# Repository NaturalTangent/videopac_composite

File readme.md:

# Videopac G7000 Composite Video

This is a PCB providing composite video amplification for a PAL VideoPac G7000.

Created using kicad 6.0.0

## Schematic

The schematic is copied from https://gamesx.com/wiki/doku.php?id=av:g7000_av

## PCB

The PCB measures 60.5mm X 23.5mm.

## BOM

[videopac_rgb_bom.csv](videopac_composite_bom.csv "BOM")

## Installation

Check the schematic for your variant of Videopac PCB, I'm led to believe that different revisions have different IC references and locations.

On the revision I tested with the IC are located as illustrated below (I desoldered the shield to access IC679 to confirm its identity, it's not essntial to do this);

Viewing from the top of the PCB, the location of the input pins are illustrated below;

I soldered to the bottom of the board as shown below;

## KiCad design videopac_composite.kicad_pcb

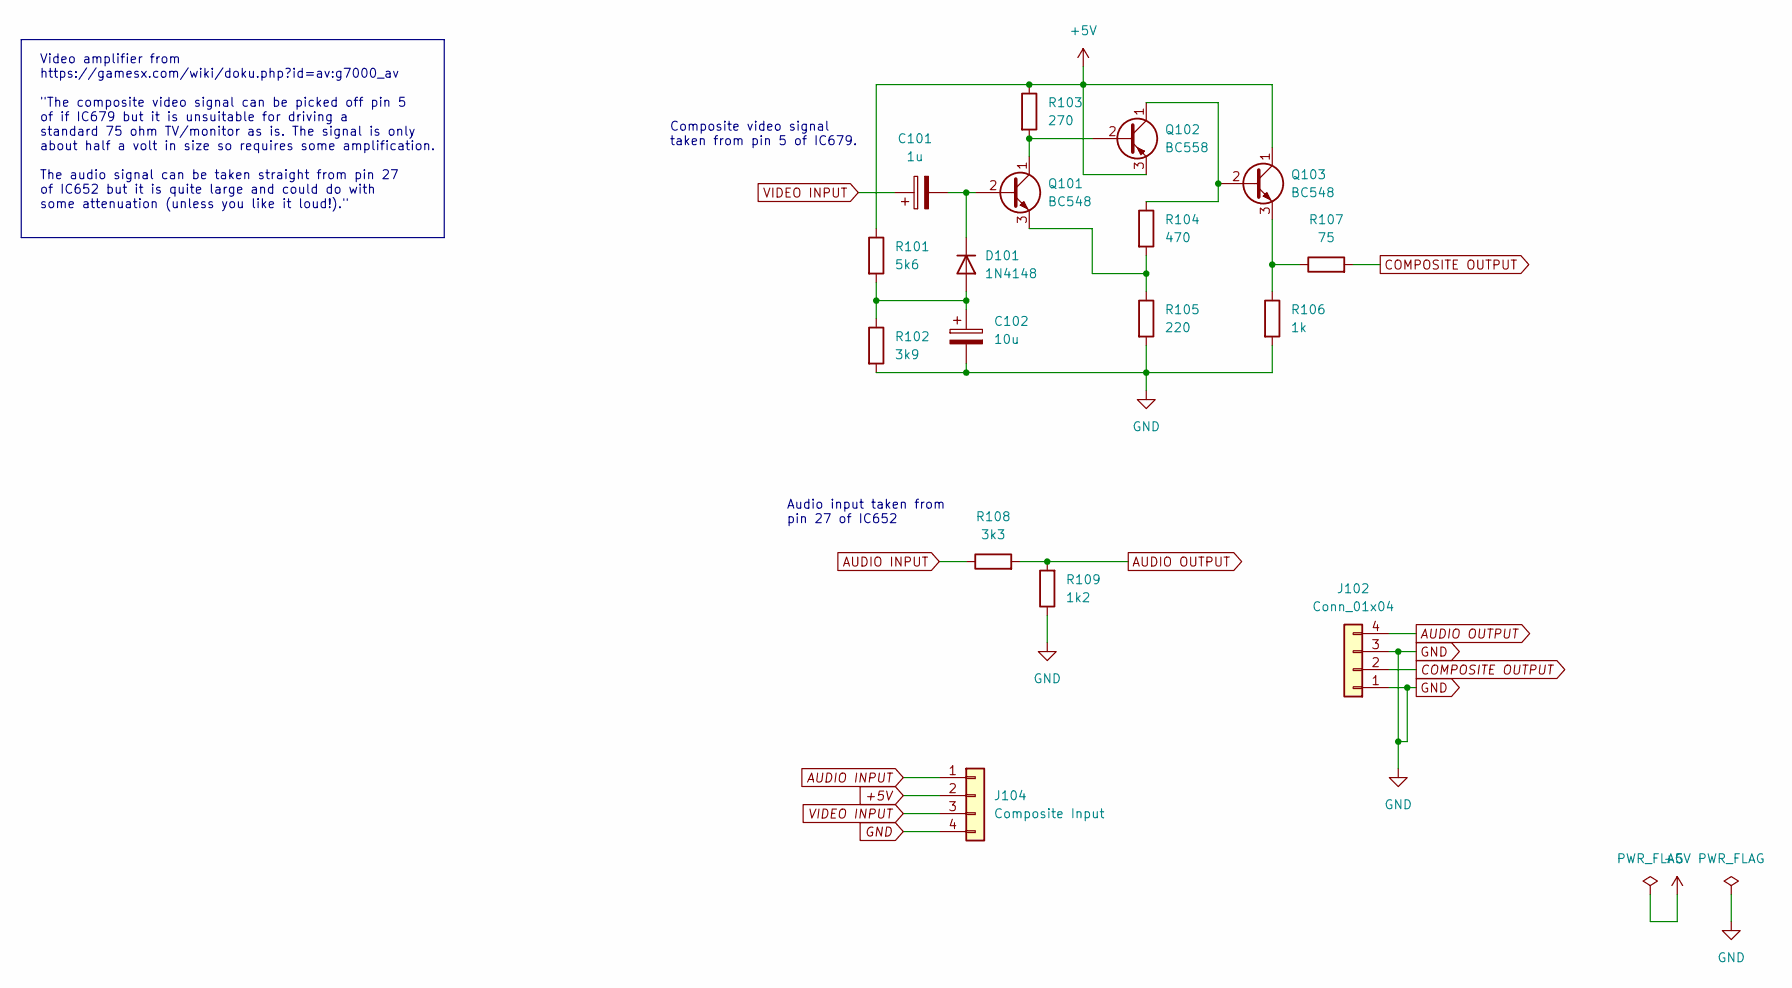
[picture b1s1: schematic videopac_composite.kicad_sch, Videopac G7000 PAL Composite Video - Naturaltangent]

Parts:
C101: 1u; CP_Radial_D5.0mm_P2.00mm
C102: 10u; CP_Radial_D5.0mm_P2.00mm
D101: 1N4148; D_DO-35_SOD27_P7.62mm_Horizontal
J102: Conn_01x04; PinHeader_1x04_P2.54mm_Horizontal
J104: Composite Input; PinHeader_1x04_P2.54mm_Horizontal
Q101, Q103: BC548; TO-92_Inline
Q102: BC558; TO-92_Inline
R101: 5k6; R_Axial_DIN0207_L6.3mm_D2.5mm_P10.16mm_Horizontal
R102: 3k9; R_Axial_DIN0207_L6.3mm_D2.5mm_P10.16mm_Horizontal
R103: 270; R_Axial_DIN0207_L6.3mm_D2.5mm_P10.16mm_Horizontal
R104: 470; R_Axial_DIN0207_L6.3mm_D2.5mm_P10.16mm_Horizontal
R105: 220; R_Axial_DIN0207_L6.3mm_D2.5mm_P10.16mm_Horizontal
R106: 1k; R_Axial_DIN0207_L6.3mm_D2.5mm_P10.16mm_Horizontal
R107: 75; R_Axial_DIN0207_L6.3mm_D2.5mm_P10.16mm_Horizontal
R108: 3k3; R_Axial_DIN0207_L6.3mm_D2.5mm_P10.16mm_Horizontal
R109: 1k2; R_Axial_DIN0207_L6.3mm_D2.5mm_P10.16mm_Horizontal

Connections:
+5V: J104.2, Q102.3 (E), Q103.1 (C), R101.1, R103.1
AUDIO INPUT: J104.1, R108.1
AUDIO OUTPUT: J102.4, R108.2, R109.2
COMPOSITE OUTPUT: J102.2, R107.2
GND: C102.2, J102.1, J102.3, J104.4, R102.2, R105.2, R106.2, R109.1
unnamed: C101.2, D101.1 (K), Q101.2 (B)
unnamed: C102.1, D101.2 (A), R101.2, R102.1
unnamed: Q101.1 (C), Q102.2 (B), R103.2
unnamed: Q101.3 (E), R104.2, R105.1
unnamed: Q102.1 (C), Q103.2 (B), R104.1
unnamed: Q103.3 (E), R106.1, R107.1
VIDEO INPUT: C101.1, J104.3

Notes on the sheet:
Video amplifier from https://gamesx.com/wiki/doku.php?id=av:g7000_av "The composite video signal can be picked off pin 5 of if IC679 but it is unsuitable for driving a standard 75 ohm TV/monitor as is. The signal is only about half a volt in size so requires some amplification. The audio signal can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
Audio input taken from pin 27 of IC652
Composite video signal taken from pin 5 of IC679.

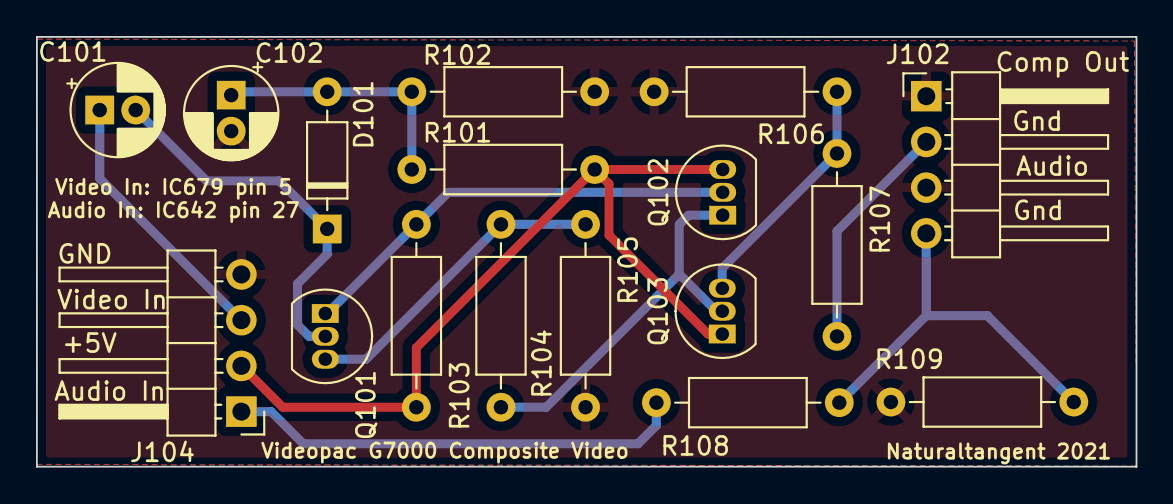
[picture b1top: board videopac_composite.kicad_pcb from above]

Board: 2 copper layers, 61.1 x 23.9 mm, 17 parts (0 on the bottom side), 12 nets.

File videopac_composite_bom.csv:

"Id";"Designator";"Package";"Quantity";"Designation";"Supplier and ref";
1;"J102";"PinHeader_1x04_P2.54mm_Horizontal";1;"Conn_01x04";;;
2;"C101";"CP_Radial_D5.0mm_P2.00mm";1;"1u";;;
3;"R108";"R_Axial_DIN0207_L6.3mm_D2.5mm_P10.16mm_Horizontal";1;"3k3";;;
4;"Q102";"TO-92_Inline";1;"BC558";;;
5;"R105";"R_Axial_DIN0207_L6.3mm_D2.5mm_P10.16mm_Horizontal";1;"220";;;
6;"R107";"R_Axial_DIN0207_L6.3mm_D2.5mm_P10.16mm_Horizontal";1;"75";;;
7;"Q101,Q103";"TO-92_Inline";2;"BC548";;;
8;"R103";"R_Axial_DIN0207_L6.3mm_D2.5mm_P10.16mm_Horizontal";1;"270";;;
9;"C102";"CP_Radial_D5.0mm_P2.00mm";1;"10u";;;
10;"R102";"R_Axial_DIN0207_L6.3mm_D2.5mm_P10.16mm_Horizontal";1;"3k9";;;
11;"R104";"R_Axial_DIN0207_L6.3mm_D2.5mm_P10.16mm_Horizontal";1;"470";;;
12;"R106";"R_Axial_DIN0207_L6.3mm_D2.5mm_P10.16mm_Horizontal";1;"1k";;;
13;"D101";"D_DO-35_SOD27_P7.62mm_Horizontal";1;"1N4148";;;
14;"R109";"R_Axial_DIN0207_L6.3mm_D2.5mm_P10.16mm_Horizontal";1;"1k2";;;
15;"R101";"R_Axial_DIN0207_L6.3mm_D2.5mm_P10.16mm_Horizontal";1;"5k6";;;
16;"J104";"PinHeader_1x04_P2.54mm_Horizontal";1;"Composite Input";;;

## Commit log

2021-12-31 Initial commit of Philips Videopac G7000 composite amplifier. Untested, waiting for boards to arrive.
2021-12-31 Added bill of materials.
2022-01-14 Add additional ground connections.
2022-01-14 Add installation images to readme.
2022-01-14 Fix typo in readme.
2022-01-14 Clarify readme, it's mot essential to desolder the shield.
